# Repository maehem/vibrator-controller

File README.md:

# vibrator-controller
ESP32 based vibrator controller

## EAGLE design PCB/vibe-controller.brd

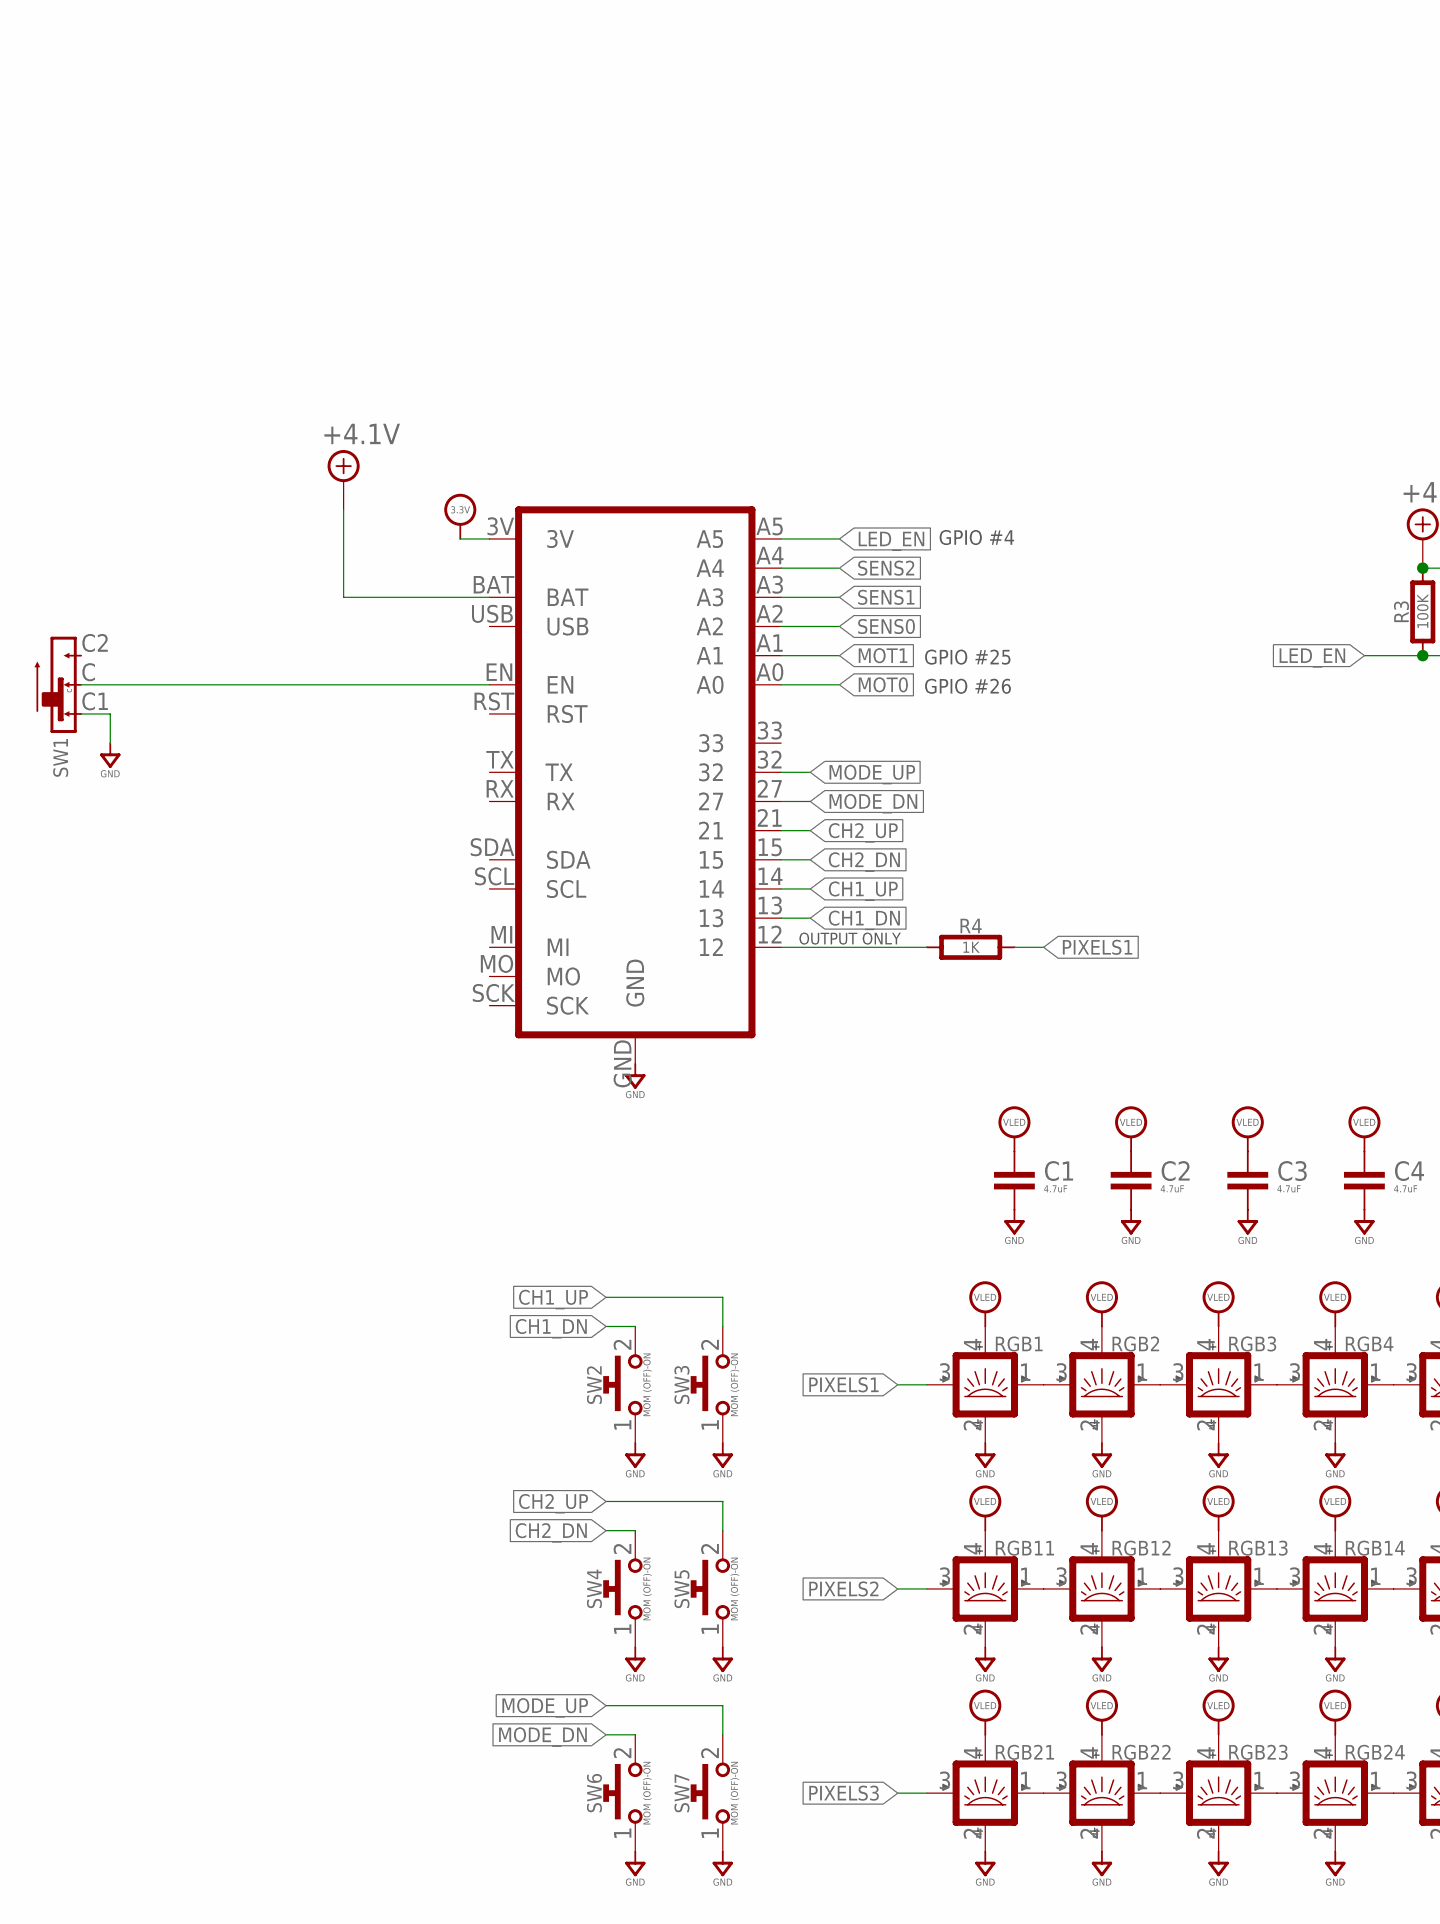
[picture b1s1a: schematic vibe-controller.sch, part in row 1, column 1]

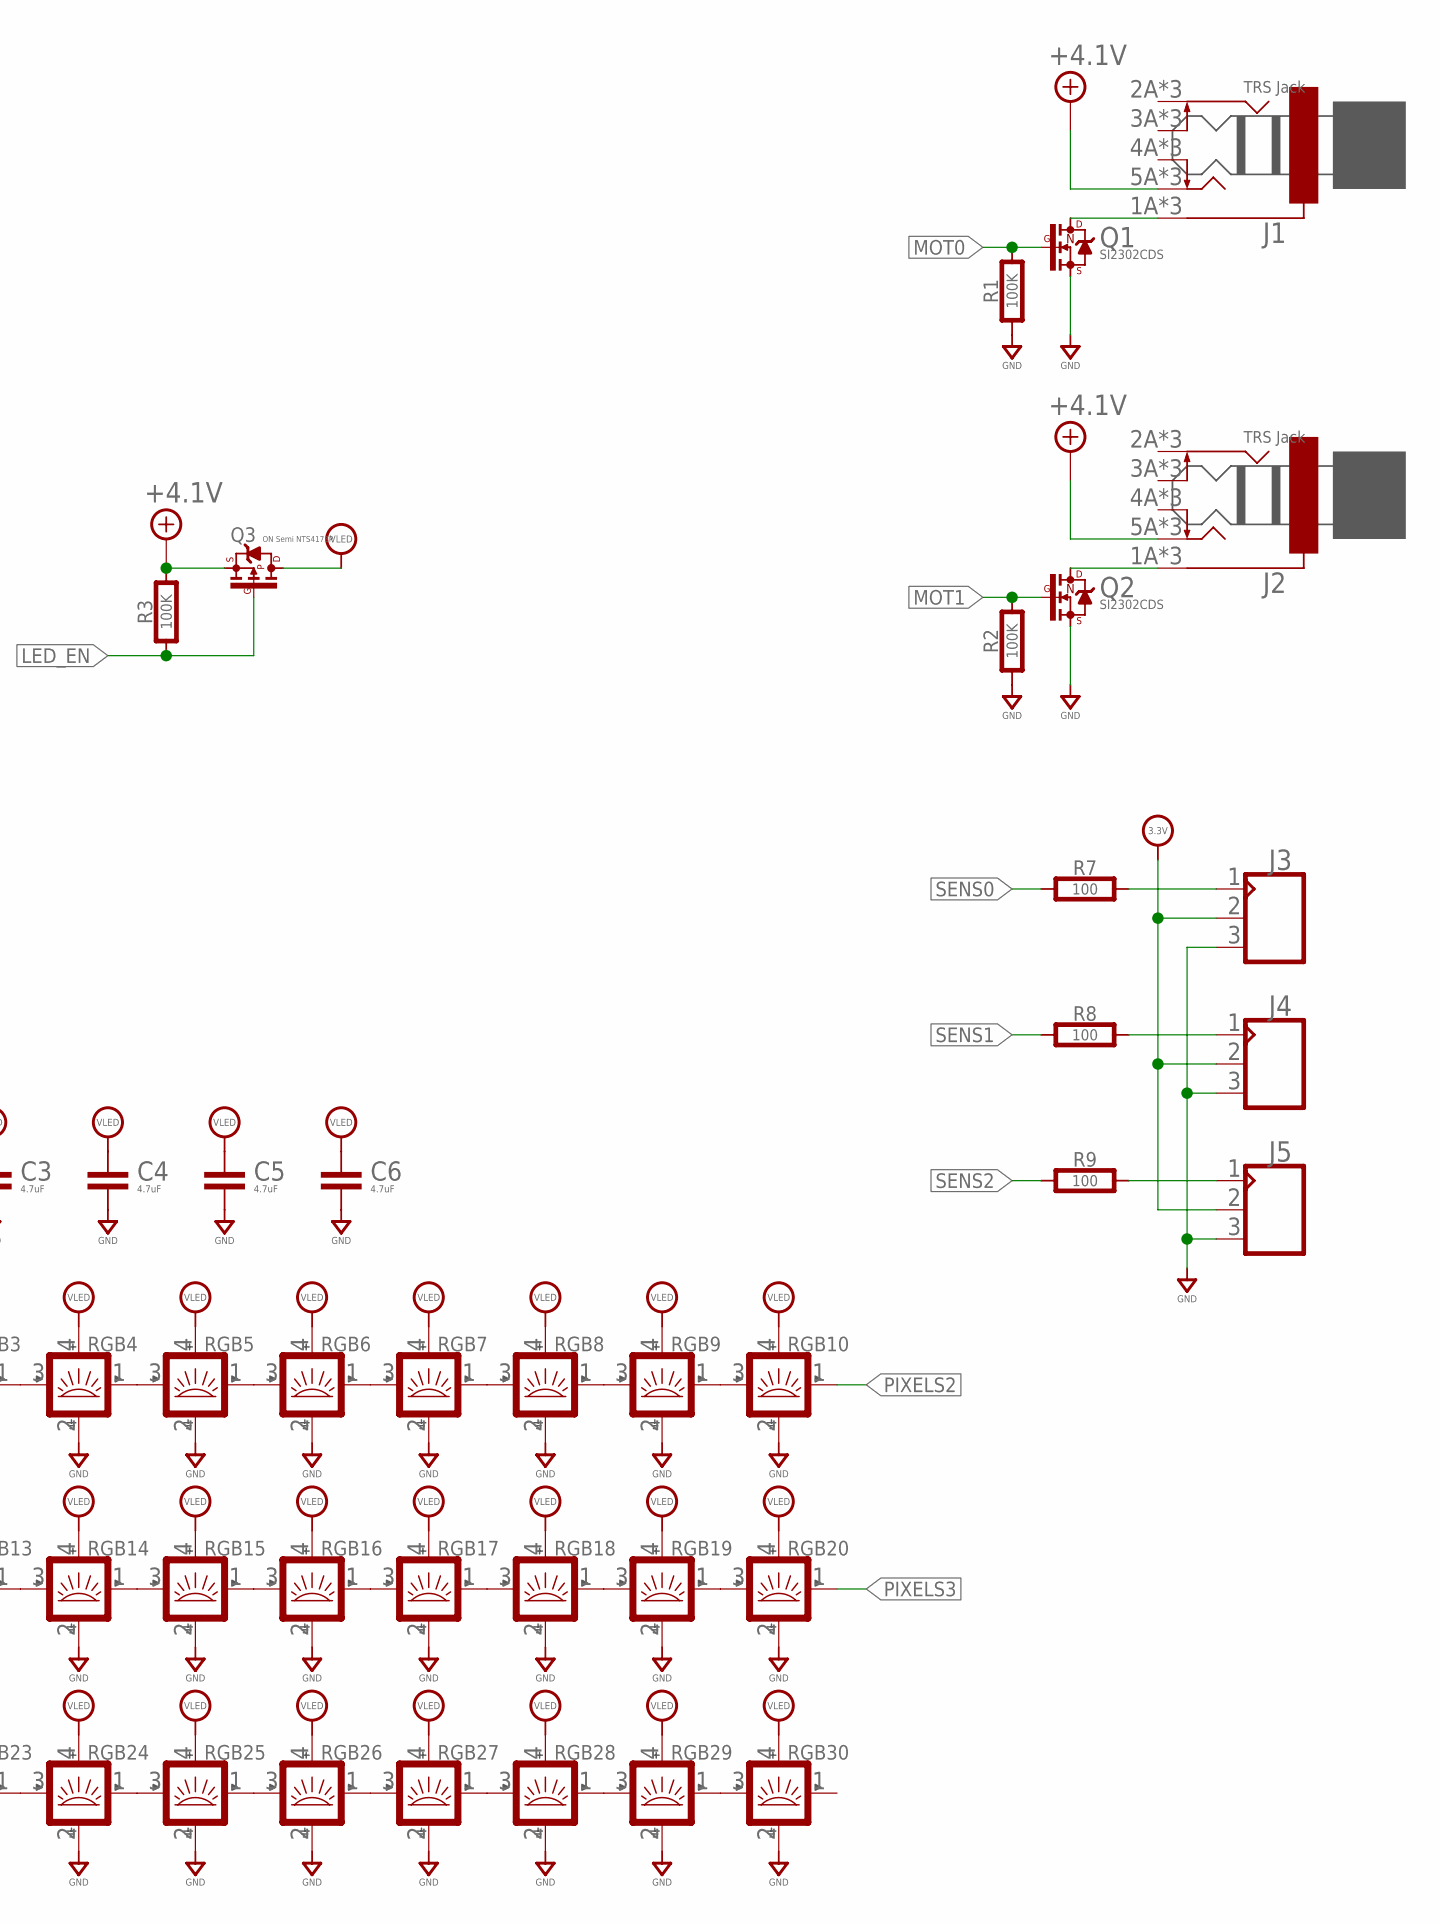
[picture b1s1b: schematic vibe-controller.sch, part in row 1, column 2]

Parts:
C1, C2, C3, C4, C5, C6: 4.7uF; 0603-CAP
HUZ1: HUZZAHHUZZAH; ADAFRUIT_HUZZAH32
J1, J2: TRS Jack; PJ-324
J3, J4, J5: CON_03X1-2.54MM-THD-RA; MA03X1-RA-THD
Q1, Q2: SI2302CDS; SOT-23
Q3: ON Semi NTS4173P; SOT-323
R1, R2, R3: 100K; 0603-RES
R4: 1K; 0603-RES
R7, R8, R9: 100; 0603-RES
RGB1, RGB2, RGB3, RGB4, RGB5, RGB6, RGB7, RGB8, RGB9, RGB10, RGB11, RGB12, RGB13, RGB14, RGB15, RGB16, RGB17, RGB18, RGB19, RGB20, RGB21, RGB22, RGB23, RGB24, RGB25, RGB26, RGB27, RGB28, RGB29, RGB30: SMART_LED3535; SMD_3535
SW1: SLIDE-SPDT-SSSS; ALPS_SSSS810701
SW2, SW3, SW4, SW5, SW6, SW7: MOM (OFF)-ON; SWITCH-0635-2P-SMD

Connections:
+3.3V: HUZ1.3V, J3.2, J4.2, J5.2
+4.1V: HUZ1.BAT, J1.5A (T), J1.5A1 (T), J1.5A2 (T), J2.5A (T), J2.5A1 (T), J2.5A2 (T), Q3.2 (S), R3.2
CH1_DN: HUZ1.13, SW2.2
CH1_UP: HUZ1.14, SW3.2
CH2_DN: HUZ1.15, SW4.2
CH2_UP: HUZ1.21, SW5.2
GND: C1.2, C2.2, C3.2, C4.2, C5.2, C6.2, HUZ1.GND, J3.3, J4.3, J5.3, Q1.2 (S), Q2.2 (S), R1.1, R2.1, RGB1.2 (GND), RGB2.2 (GND), RGB3.2 (GND), RGB4.2 (GND), RGB5.2 (GND), RGB6.2 (GND), RGB7.2 (GND), RGB8.2 (GND), RGB9.2 (GND), RGB10.2 (GND), RGB11.2 (GND), RGB12.2 (GND), RGB13.2 (GND), RGB14.2 (GND), RGB15.2 (GND), RGB16.2 (GND), RGB17.2 (GND), RGB18.2 (GND), RGB19.2 (GND), RGB20.2 (GND), RGB21.2 (GND), RGB22.2 (GND), RGB23.2 (GND), RGB24.2 (GND), RGB25.2 (GND), RGB26.2 (GND), RGB27.2 (GND), RGB28.2 (GND), RGB29.2 (GND), RGB30.2 (GND), SW1.C1 (1), SW2.1, SW3.1, SW4.1, SW5.1, SW6.1, SW7.1
LED_EN: HUZ1.A5, Q3.1 (G), R3.1
MODE_DN: HUZ1.27, SW6.2
MODE_UP: HUZ1.32, SW7.2
MOT0: HUZ1.A0, Q1.1 (G), R1.2
MOT1: HUZ1.A1, Q2.1 (G), R2.2
unnamed: HUZ1.EN, SW1.C (2)
unnamed: J1.1A (S), J1.1A1 (S), J1.1A2 (S), Q1.3 (D)
unnamed: J2.1A (S), J2.1A1 (S), J2.1A2 (S), Q2.3 (D)
unnamed: RGB11.1 (OUT), RGB12.3 (IN)
unnamed: RGB1.1 (OUT), RGB2.3 (IN)
unnamed: RGB2.1 (OUT), RGB3.3 (IN)
unnamed: RGB3.1 (OUT), RGB4.3 (IN)
unnamed: RGB4.1 (OUT), RGB5.3 (IN)
unnamed: RGB5.1 (OUT), RGB6.3 (IN)
unnamed: RGB6.1 (OUT), RGB7.3 (IN)
unnamed: RGB7.1 (OUT), RGB8.3 (IN)
unnamed: RGB8.1 (OUT), RGB9.3 (IN)
unnamed: RGB9.1 (OUT), RGB10.3 (IN)
unnamed: RGB12.1 (OUT), RGB13.3 (IN)
unnamed: RGB13.1 (OUT), RGB14.3 (IN)
unnamed: RGB14.1 (OUT), RGB15.3 (IN)
unnamed: RGB15.1 (OUT), RGB16.3 (IN)
unnamed: RGB16.1 (OUT), RGB17.3 (IN)
unnamed: RGB17.1 (OUT), RGB18.3 (IN)
unnamed: RGB18.1 (OUT), RGB19.3 (IN)
unnamed: RGB19.1 (OUT), RGB20.3 (IN)
unnamed: RGB21.1 (OUT), RGB22.3 (IN)
unnamed: RGB22.1 (OUT), RGB23.3 (IN)
unnamed: RGB23.1 (OUT), RGB24.3 (IN)
unnamed: RGB24.1 (OUT), RGB25.3 (IN)
unnamed: RGB25.1 (OUT), RGB26.3 (IN)
unnamed: RGB26.1 (OUT), RGB27.3 (IN)
unnamed: RGB27.1 (OUT), RGB28.3 (IN)
unnamed: RGB28.1 (OUT), RGB29.3 (IN)
unnamed: RGB29.1 (OUT), RGB30.3 (IN)
unnamed: HUZ1.12, R4.1
unnamed: J3.1, R7.2
unnamed: J4.1, R8.2
unnamed: J5.1, R9.2
PIXELS1: R4.2, RGB1.3 (IN)
PIXELS2: RGB10.1 (OUT), RGB11.3 (IN)
PIXELS3: RGB20.1 (OUT), RGB21.3 (IN)
SENS0: HUZ1.A2, R7.1
SENS1: HUZ1.A3, R8.1
SENS2: HUZ1.A4, R9.1
VLED: C1.1, C2.1, C3.1, C4.1, C5.1, C6.1, Q3.3 (D), RGB1.4 (VDD), RGB2.4 (VDD), RGB3.4 (VDD), RGB4.4 (VDD), RGB5.4 (VDD), RGB6.4 (VDD), RGB7.4 (VDD), RGB8.4 (VDD), RGB9.4 (VDD), RGB10.4 (VDD), RGB11.4 (VDD), RGB12.4 (VDD), RGB13.4 (VDD), RGB14.4 (VDD), RGB15.4 (VDD), RGB16.4 (VDD), RGB17.4 (VDD), RGB18.4 (VDD), RGB19.4 (VDD), RGB20.4 (VDD), RGB21.4 (VDD), RGB22.4 (VDD), RGB23.4 (VDD), RGB24.4 (VDD), RGB25.4 (VDD), RGB26.4 (VDD), RGB27.4 (VDD), RGB28.4 (VDD), RGB29.4 (VDD), RGB30.4 (VDD)

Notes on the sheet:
OUTPUT ONLY
GPIO #4
GPIO #26
GPIO #25

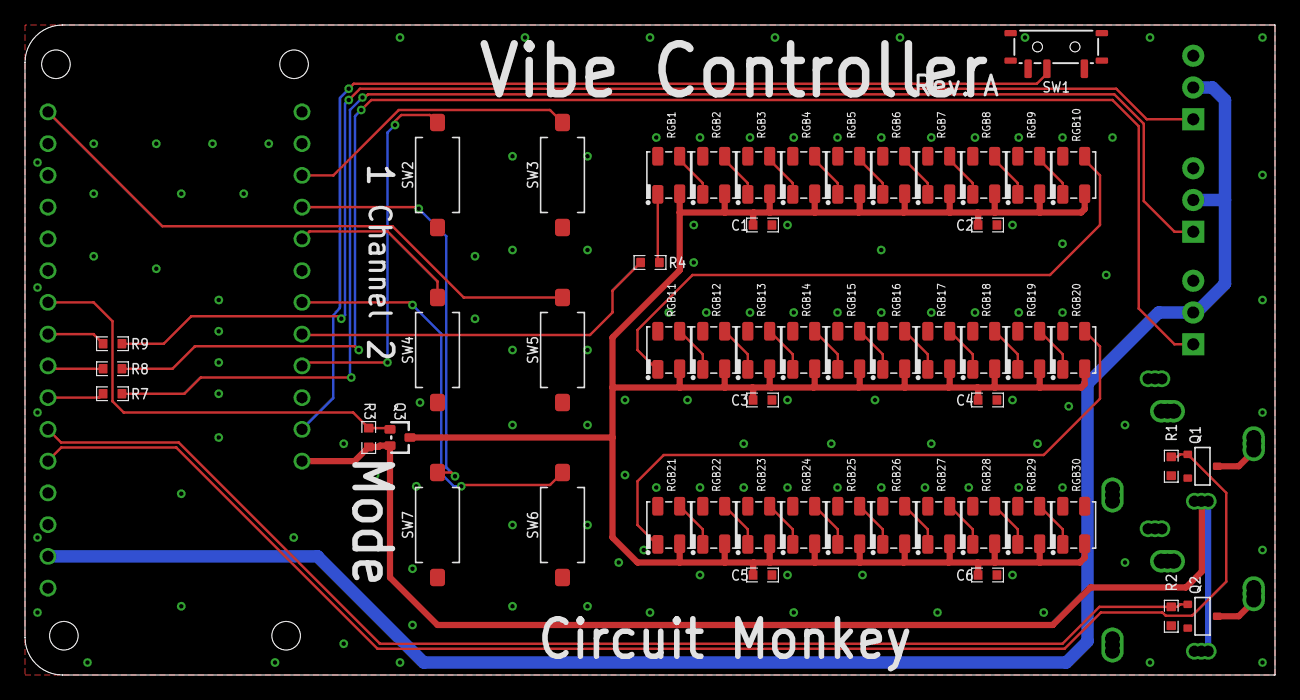
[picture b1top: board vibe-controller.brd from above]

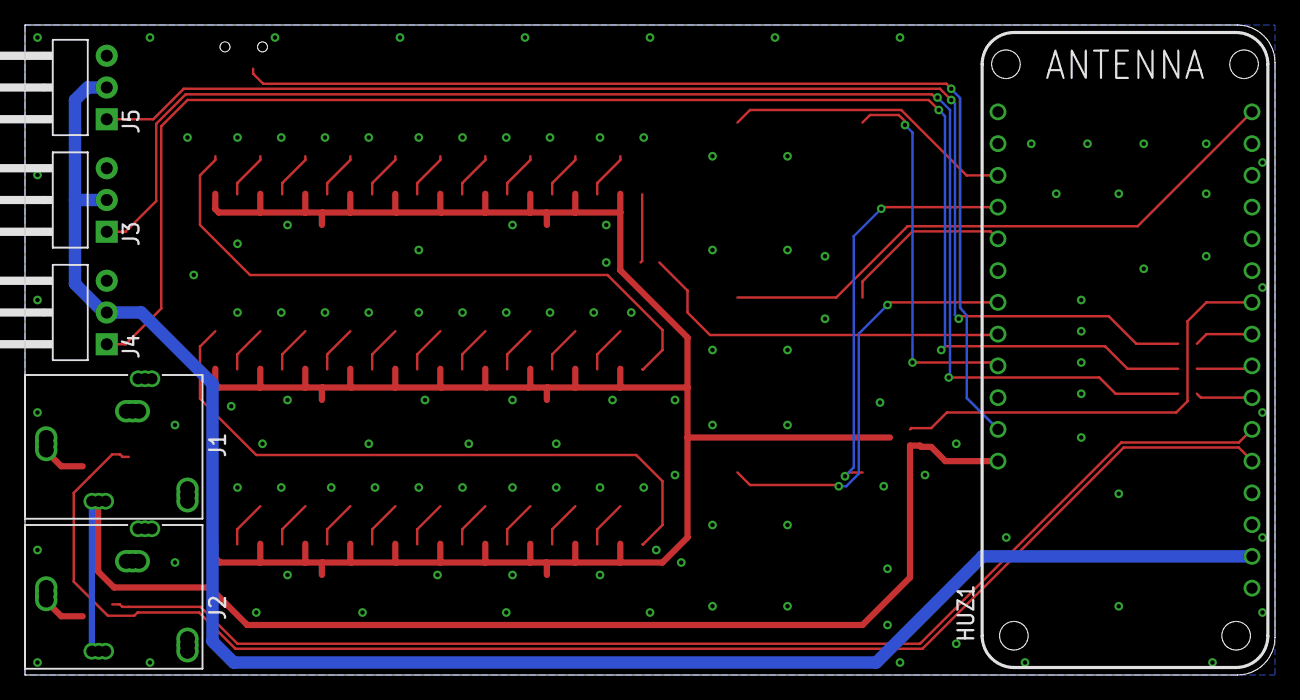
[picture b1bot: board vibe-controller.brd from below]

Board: 2 copper layers, 100.0 x 52.0 mm, 59 parts (6 on the bottom side), 53 nets.

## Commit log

2021-12-29 Rev. A Board sent to FAB.
2022-02-04 Basic Code working
2022-04-15 Build notes
